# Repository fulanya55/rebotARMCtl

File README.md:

# rebotARMCtl

机械臂采集部署平台与 STM32 同步控制器，面向 reBot Arm B601-RS 与 Star Arm 102。

> **当前状态：软件、固件和 PCB 设计已完成，但都还没有接触过真实硬件。** 固件只在 PC 上的仿真器里运行过，STM32 镜像只完成了编译和结构检查，电路板还没有打样。第一次接机械臂前，请按 [docs/bringup.md](docs/bringup.md) 一步步做。

## 没有硬件时先跑起来

需要 [uv](https://docs.astral.sh/uv/) 和 Node.js。

```bash
uv sync
cd apps/lab/frontend && npm ci && npm run build && cd ../../..
uv run rac up --sim
```

打开 <http://127.0.0.1:8000/controller>。`--sim` 用的是真实的固件核心加一个机械臂仿真器，协议和总线时序都按真实设备走。接上控制器后，把 `--sim` 去掉即可。

## 能做什么

| 需求 | 功能 | 位置 |
| --- | --- | --- |
| 1.1 设备连接 | 控制器发现和重连、端口型号识别、机械臂绑定、相机预览和保存绑定 | 控制台「设备」页 |
| 1.2 关节校准 | 按序列号保存的校准版本，零位、方向、行程范围和夹爪标定，单关节验证 | 「校准」页 |
| 1.3 主从同步 | **在 STM32 上本地闭环**，PC 的卡顿不影响跟随；PC 断开 500 ms 后全部机械臂进入保持 | `firmware/core` |
| 1.4 可视化示教 | URDF 三维视图、关节滑块和拖动、末端拖动（PC 上解 IK）、示教点、RS 拖动示教 | 「示教」页 |
| 1.5 模型部署 | LeRobot 和 StarVLA 后端，模型放在独立进程里 | `packages/rac-policy` |
| 1.6 人工干预 | 接管和交还，过期令牌和旧代次的指令一律被拒绝 | 「模型」页 |
| 1.7 真机回放 | 从任意时间点回放，先缓慢靠近起点 | 「回放」页 |
| 1.8 统一运行控制 | 所有页面共用的状态条，停止和急停始终可用 | `RunBar` |
| 2.1–2.5 数据 | LeRobot Dataset v3 录制、原始时间线、标注、导入导出合并、浏览 | `packages/rac-data` |
| 3.1–3.3 控制器 | 2 路 CAN、2 路 UART、1 路 USB，带版本的 RAC-Link 协议，Python SDK | `firmware/`、`packages/rac-link` |

基础配置是 2 台 reBot RS 从臂加 2 台 Star 主臂。原有 MakerMods Lab 的页面和流程也保留了。`controller` 类型的机器人可以在 Lab 里遥操作和录制；回放和模型部署请用控制台页面，Lab 会直接提示，因为它的缓入逻辑按角度计算，不适用于这里以弧度工作的机械臂。

## 目录

```
apps/lab/             MakerMods Lab（已内嵌）加控制器页面和路由
packages/rac-link/    协议、传输层、Python SDK
packages/rac-service/ Controller Service，USB 的唯一持有者
packages/rac-kinematics/  URDF、正逆运动学、轨迹
packages/rac-camera/  相机进程和共享内存
packages/rac-data/    录制、LeRobot 数据集、标注
packages/rac-policy/  模型进程
packages/rac-lerobot/ LeRobot 的 Robot 和 Teleoperator 代理
firmware/core/        可移植的固件核心
firmware/port/        stm32g4（真机）和 sil（仿真）
hardware/sync-controller/  硬件选型、KiCad 工程、制造文件
tools/                协议生成、固件构建
```

设计说明见 [docs/architecture.md](docs/architecture.md)，协议见 [docs/protocol.md](docs/protocol.md)，硬件见 [hardware/sync-controller/README.md](hardware/sync-controller/README.md)。

## 常用命令

```bash
uv run pytest tests                              # 全部集成测试
uv run python tools/build_firmware.py test       # 固件核心的行为测试
uv run python tools/build_firmware.py stm32      # 交叉编译（先运行 tools/fetch_firmware_deps.py）
uv run python tools/gen_protocol.py              # 改协议后重新生成 C 和 Python
uv run python hardware/sync-controller/gen/make_all.py  # 重新生成并检查整块板子
PYTHONUTF8=1 uv run python tests/e2e/run_web_e2e.py --out <目录>  # 浏览器走查（先启动平台）
```

交叉编译用的是 `ziglang`，由 uv 管理，不需要另装 ARM 工具链。硬件部分需要 KiCad 10，路径不同时设置 `KICAD_CLI` 和 `KICAD_PYTHON`。

Lab 自带的测试要在 `apps/lab` 目录下运行，并设置 `PYTHONUTF8=1`。Windows 上有 72 个测试失败，引入控制器之前就是这 72 个，主要和路径、进程管理的平台差异有关。

## 许可

本仓库只用于个人学习，**请保持私有**：里面有几项上游没有授予再分发权利的文件。复用了哪些项目、公开前要清掉什么，都写在 [docs/LICENSE_AUDIT.md](docs/LICENSE_AUDIT.md)。代码暂定 Apache-2.0，`assets/robots/rebot_b601_rs` 沿用其 CERN-OHL-W-2.0，内嵌的 Lab 保留其上游许可。

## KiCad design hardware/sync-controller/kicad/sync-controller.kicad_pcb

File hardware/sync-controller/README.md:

# 同步控制器硬件

STM32G474 主控，2 路隔离 CAN、2 路隔离舵机 UART、USB-C、急停回路和继电器输出。116 × 90 mm，4 层板。

**这块板子还没有打样，也没有上电。** 下面的检查都是设计规则层面的，不能代替实物验证。

## 文件

| 路径 | 内容 |
| --- | --- |
| `docs/selection.md` | 选型依据，每项都写了来源 |
| `docs/bom.csv` | 物料清单。LCSC 编号留空表示还没确认，下单前要逐项核对 |
| `docs/schematic.pdf`、`docs/board_top.png` | 原理图和渲染图 |
| `gen/design.py` | **唯一的设计数据**，原理图和 PCB 都从这里生成 |
| `kicad/` | 生成的 KiCad 工程，可以直接用 KiCad 打开 |
| `fab/` | Gerber、钻孔和贴片坐标 |

## 重新生成

```bash
uv run python hardware/sync-controller/gen/make_all.py
```

顺序是原理图 → BOM → ERC → 网表比对 → 布局布线 → DRC 和原理图一致性 → 隔离带测量 → 制造文件，任何一步失败就停。布线要几分钟，`--skip-route` 可以保留现有布局。

修改设计请改 `gen/design.py` 或 `gen/gen_pcb.py`。直接在 KiCad 里改的内容，下次生成时会被覆盖；如果决定以后手工维护 PCB，就不要再运行布线这一步。

## 关键设计

- **每路接口独立隔离。** CAN 用 ISO1044BD，UART 用 ADuM1201BRZ，电源用 B0509S-1WR3 加 HT7550-1 稳压。没有用 5 V 输入 5 V 输出的模块，因为它轻载时电压可能超过 ISO1044 VCC2 的 5.5 V 上限。
- **控制板不从机械臂取电。** Star 的 3 针舵机座中间的电源针没有连接。隔离侧由板上的 DC/DC 供电。
- **急停是硬件回路。** 常闭急停触点和继电器线圈串联，按下后不经过任何软件就会释放。MCU 复位时栅极的下拉同样会让继电器释放。两路检测信号让固件也能知道发生了什么。
- **继电器只给信号用。** G5V-2 不能切断 48 V 电机电流，请用它去控制外部的接触器或驱动器使能。

## 布线

这块板子的布线由 `gen/gen_pcb.py` 里自己写的栅格 A* 布线器完成，带拆线重布和隔离域约束。它能保证 DRC 通过，但不会像有经验的工程师那样考虑回流路径、串扰和散热。**打样前请人工审一遍版图**，重点看 USB 差分对、CAN 差分对、DC/DC 周围和跨隔离带的区域。

## 打样前还要确认

- BOM 里 LCSC 编号为空的物料，以及所有封装和实物的对应关系
- Star 线束的针脚顺序和逻辑电平（目前来自公开资料，未用实物验证）
- 隔离带 1.00 mm 是**功能隔离**，不是安全隔离，不能当作安规爬电距离
- 嘉立创等厂家的 4 层板叠层和阻抗参数。USB 差分对没有做阻抗计算
- 板上没有放光学定位点（fiducial）。要贴片的话，确认厂家能接受或自行添加
- 急停端子不接急停按钮时，板子会一直处于急停状态，继电器不吸合。这是故意的，接线方法见 `docs/bringup.md` 第 2 步

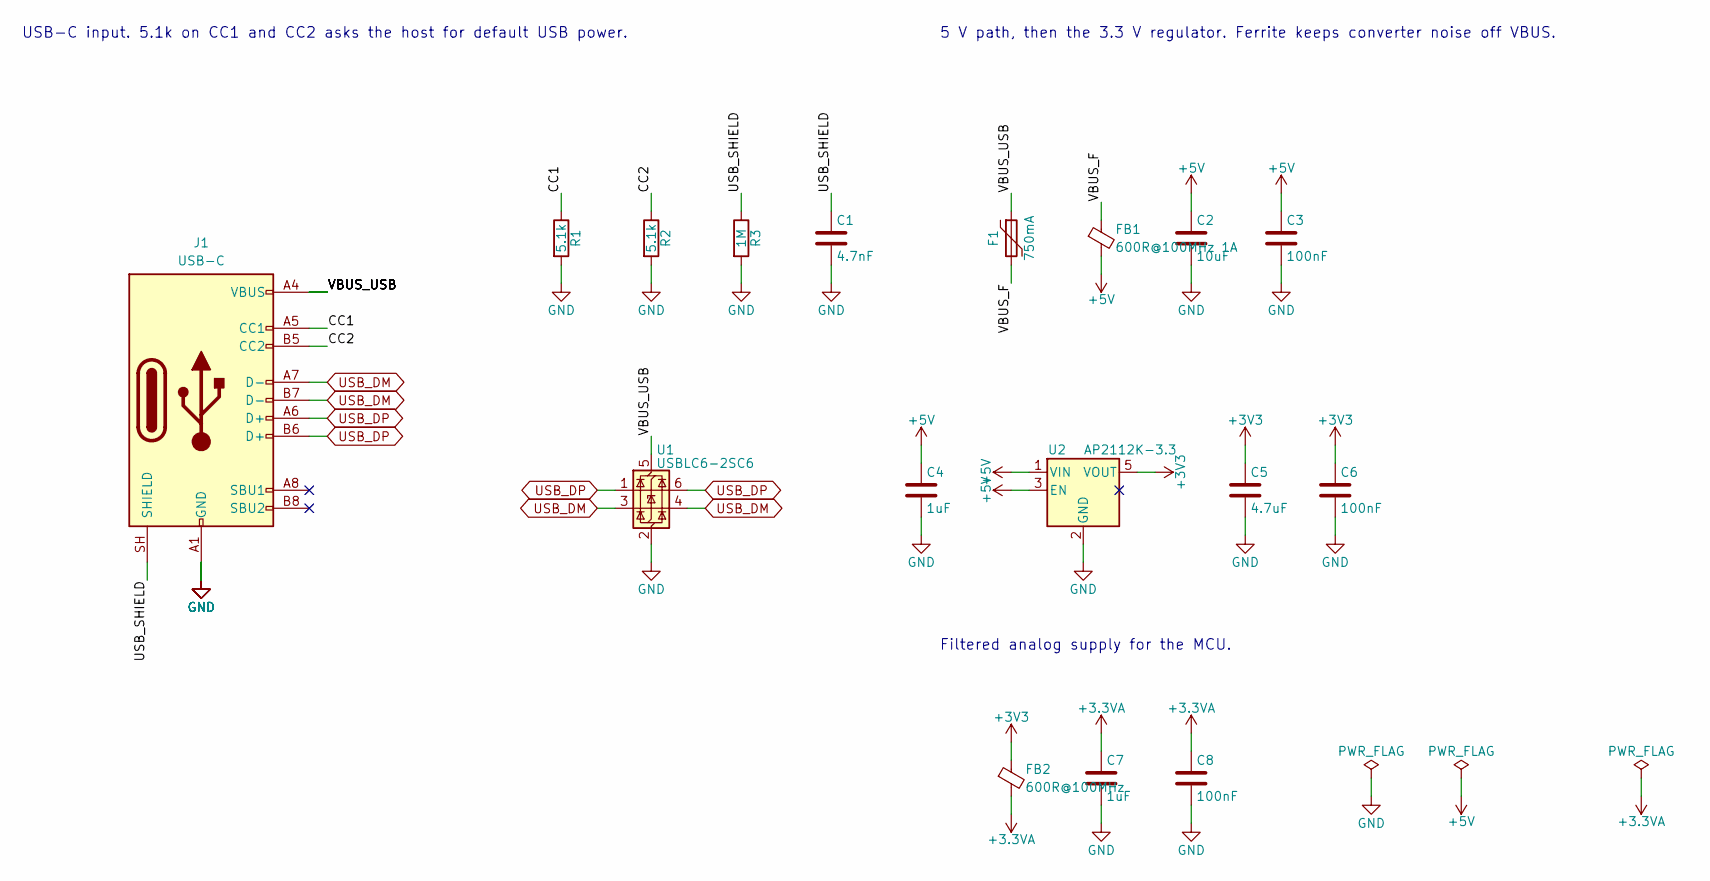
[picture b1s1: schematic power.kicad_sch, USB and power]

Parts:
C1: 4.7nF; C_0603_1608Metric
C2: 10uF; C_0805_2012Metric
C3, C6, C8: 100nF; C_0603_1608Metric
C4, C7: 1uF; C_0603_1608Metric
C5: 4.7uF; C_0805_2012Metric
F1: 750mA; Fuse_1206_3216Metric; MPN SMD1206 750mA hold
FB1: 600R@100MHz 1A; L_0805_2012Metric
FB2: 600R@100MHz; L_0603_1608Metric
J1: USB-C; USB_C_Receptacle_HRO_TYPE-C-31-M-12; MPN HRO TYPE-C-31-M-12; LCSC C165948
R1, R2: 5.1k; R_0603_1608Metric
R3: 1M; R_0603_1608Metric
U1: USBLC6-2SC6; SOT-23-6; MPN USBLC6-2SC6
U2: AP2112K-3.3; SOT-23-5; MPN AP2112K-3.3TRG1

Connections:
+3.3VA: C7.1, C8.1, FB2.2; also elsewhere on the board
+3V3: C5.1, C6.1, FB2.1, U2.5 (VOUT); also elsewhere on the board
+5V: C2.1, C3.1, C4.1, FB1.2, U2.1 (VIN), U2.3 (EN); also elsewhere on the board
/USB and power/CC1: J1.A5 (CC1), R1.1
/USB and power/CC2: J1.B5 (CC2), R2.1
/USB and power/USB_SHIELD: C1.1, J1.SH (SHIELD), R3.1
/USB and power/VBUS_F: F1.2, FB1.1
/USB and power/VBUS_USB: F1.1, J1.A4 (VBUS), J1.A9 (VBUS), J1.B4 (VBUS), J1.B9 (VBUS), U1.5 (VBUS)
GND: C1.2, C2.2, C3.2, C4.2, C5.2, C6.2, C7.2, C8.2, J1.A1 (GND), J1.A12 (GND), J1.B1 (GND), J1.B12 (GND), R1.2, R2.2, R3.2, U1.2 (GND), U2.2 (GND); also elsewhere on the board
USB_DM: J1.A7 (D-), J1.B7 (D-), U1.3 (I/O2), U1.4 (I/O2); also elsewhere on the board
USB_DP: J1.A6 (D+), J1.B6 (D+), U1.1 (I/O1), U1.6 (I/O1); also elsewhere on the board

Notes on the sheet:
USB-C input. 5.1k on CC1 and CC2 asks the host for default USB power.
5 V path, then the 3.3 V regulator. Ferrite keeps converter noise off VBUS.
Filtered analog supply for the MCU.

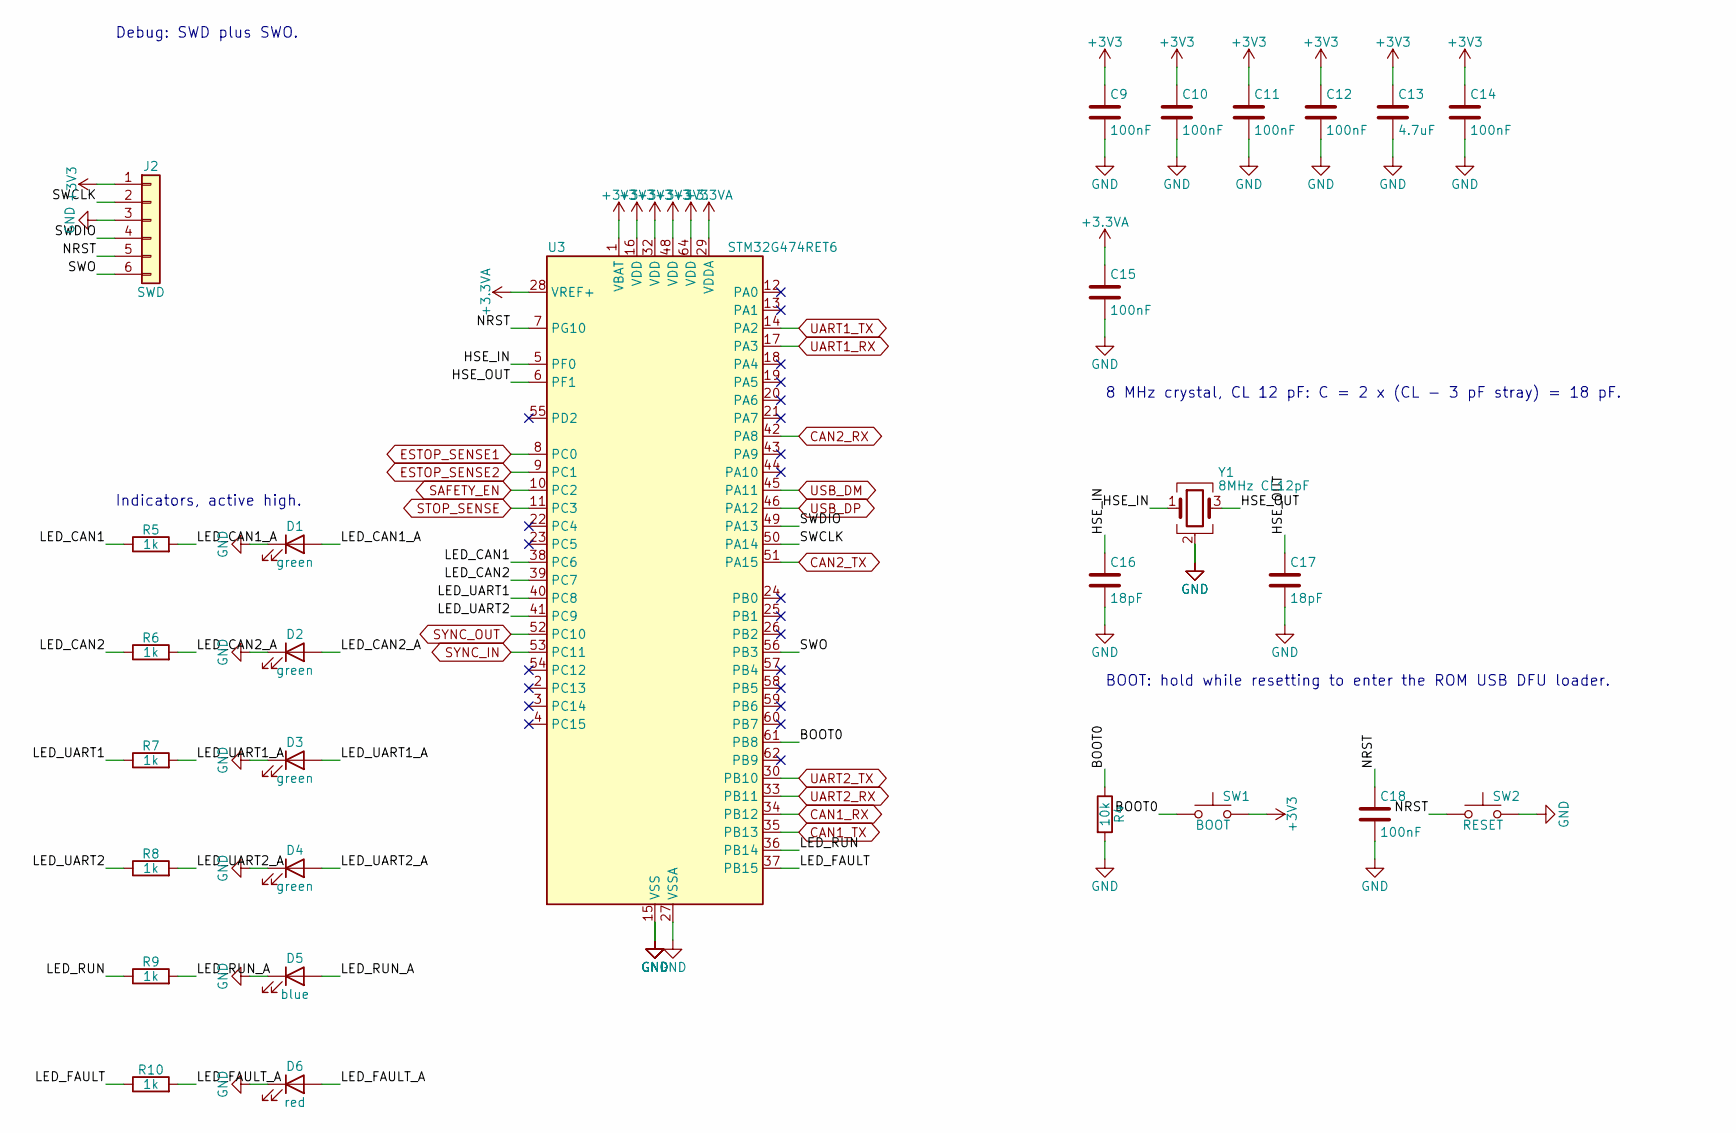
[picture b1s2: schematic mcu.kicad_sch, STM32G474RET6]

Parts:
C9, C10, C11, C12, C14, C15, C18: 100nF; C_0603_1608Metric
C13: 4.7uF; C_0805_2012Metric
C16, C17: 18pF; C_0603_1608Metric
D1, D2, D3, D4: green; LED_0603_1608Metric
D5: blue; LED_0603_1608Metric
D6: red; LED_0603_1608Metric
J2: SWD; PinHeader_1x06_P2.54mm_Vertical
R4: 10k; R_0603_1608Metric
R5, R6, R7, R8, R9, R10: 1k; R_0603_1608Metric
SW1: BOOT; SW_PUSH_6mm
SW2: RESET; SW_PUSH_6mm
U3: STM32G474RET6; LQFP-64_10x10mm_P0.5mm; MPN STM32G474RET6
Y1: 8MHz CL12pF; Crystal_SMD_3225-4Pin_3.2x2.5mm; MPN 8 MHz 3225 12 pF

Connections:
+3.3VA: C15.1, U3.28 (VREF+), U3.29 (VDDA); also elsewhere on the board
+3V3: C9.1, C10.1, C11.1, C12.1, C13.1, C14.1, J2.1, SW1.2, U3.1 (VBAT), U3.16 (VDD), U3.32 (VDD), U3.48 (VDD), U3.64 (VDD); also elsewhere on the board
/STM32G474RET6/BOOT0: R4.1, SW1.1, U3.61 (PB8)
/STM32G474RET6/HSE_IN: C16.1, U3.5 (PF0), Y1.1
/STM32G474RET6/HSE_OUT: C17.1, U3.6 (PF1), Y1.3
/STM32G474RET6/LED_CAN1: R5.1, U3.38 (PC6)
/STM32G474RET6/LED_CAN1_A: D1.2 (A), R5.2
/STM32G474RET6/LED_CAN2: R6.1, U3.39 (PC7)
/STM32G474RET6/LED_CAN2_A: D2.2 (A), R6.2
/STM32G474RET6/LED_FAULT: R10.1, U3.37 (PB15)
/STM32G474RET6/LED_FAULT_A: D6.2 (A), R10.2
/STM32G474RET6/LED_RUN: R9.1, U3.36 (PB14)
/STM32G474RET6/LED_RUN_A: D5.2 (A), R9.2
/STM32G474RET6/LED_UART1: R7.1, U3.40 (PC8)
/STM32G474RET6/LED_UART1_A: D3.2 (A), R7.2
/STM32G474RET6/LED_UART2: R8.1, U3.41 (PC9)
/STM32G474RET6/LED_UART2_A: D4.2 (A), R8.2
/STM32G474RET6/NRST: C18.1, J2.5, SW2.1, U3.7 (PG10)
/STM32G474RET6/SWCLK: J2.2, U3.50 (PA14)
/STM32G474RET6/SWDIO: J2.4, U3.49 (PA13)
/STM32G474RET6/SWO: J2.6, U3.56 (PB3)
CAN1_RX: U3.34 (PB12); also elsewhere on the board
CAN1_TX: U3.35 (PB13); also elsewhere on the board
CAN2_RX: U3.42 (PA8); also elsewhere on the board
CAN2_TX: U3.51 (PA15); also elsewhere on the board
ESTOP_SENSE1: U3.8 (PC0); also elsewhere on the board
ESTOP_SENSE2: U3.9 (PC1); also elsewhere on the board
GND: C9.2, C10.2, C11.2, C12.2, C13.2, C14.2, C15.2, C16.2, C17.2, C18.2, D1.1 (K), D2.1 (K), D3.1 (K), D4.1 (K), D5.1 (K), D6.1 (K), J2.3, R4.2, SW2.2, U3.15 (VSS), U3.27 (VSSA), U3.31 (VSS), U3.47 (VSS), U3.63 (VSS), Y1.2 (G), Y1.4 (G); also elsewhere on the board
SAFETY_EN: U3.10 (PC2); also elsewhere on the board
STOP_SENSE: U3.11 (PC3); also elsewhere on the board
SYNC_IN: U3.53 (PC11); also elsewhere on the board
SYNC_OUT: U3.52 (PC10); also elsewhere on the board
UART1_RX: U3.17 (PA3); also elsewhere on the board
UART1_TX: U3.14 (PA2); also elsewhere on the board
UART2_RX: U3.33 (PB11); also elsewhere on the board
UART2_TX: U3.30 (PB10); also elsewhere on the board
USB_DM: U3.45 (PA11); also elsewhere on the board
USB_DP: U3.46 (PA12); also elsewhere on the board

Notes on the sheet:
8 MHz crystal, CL 12 pF: C = 2 x (CL - 3 pF stray) = 18 pF.
BOOT: hold while resetting to enter the ROM USB DFU loader.
Debug: SWD plus SWO.
Indicators, active high.

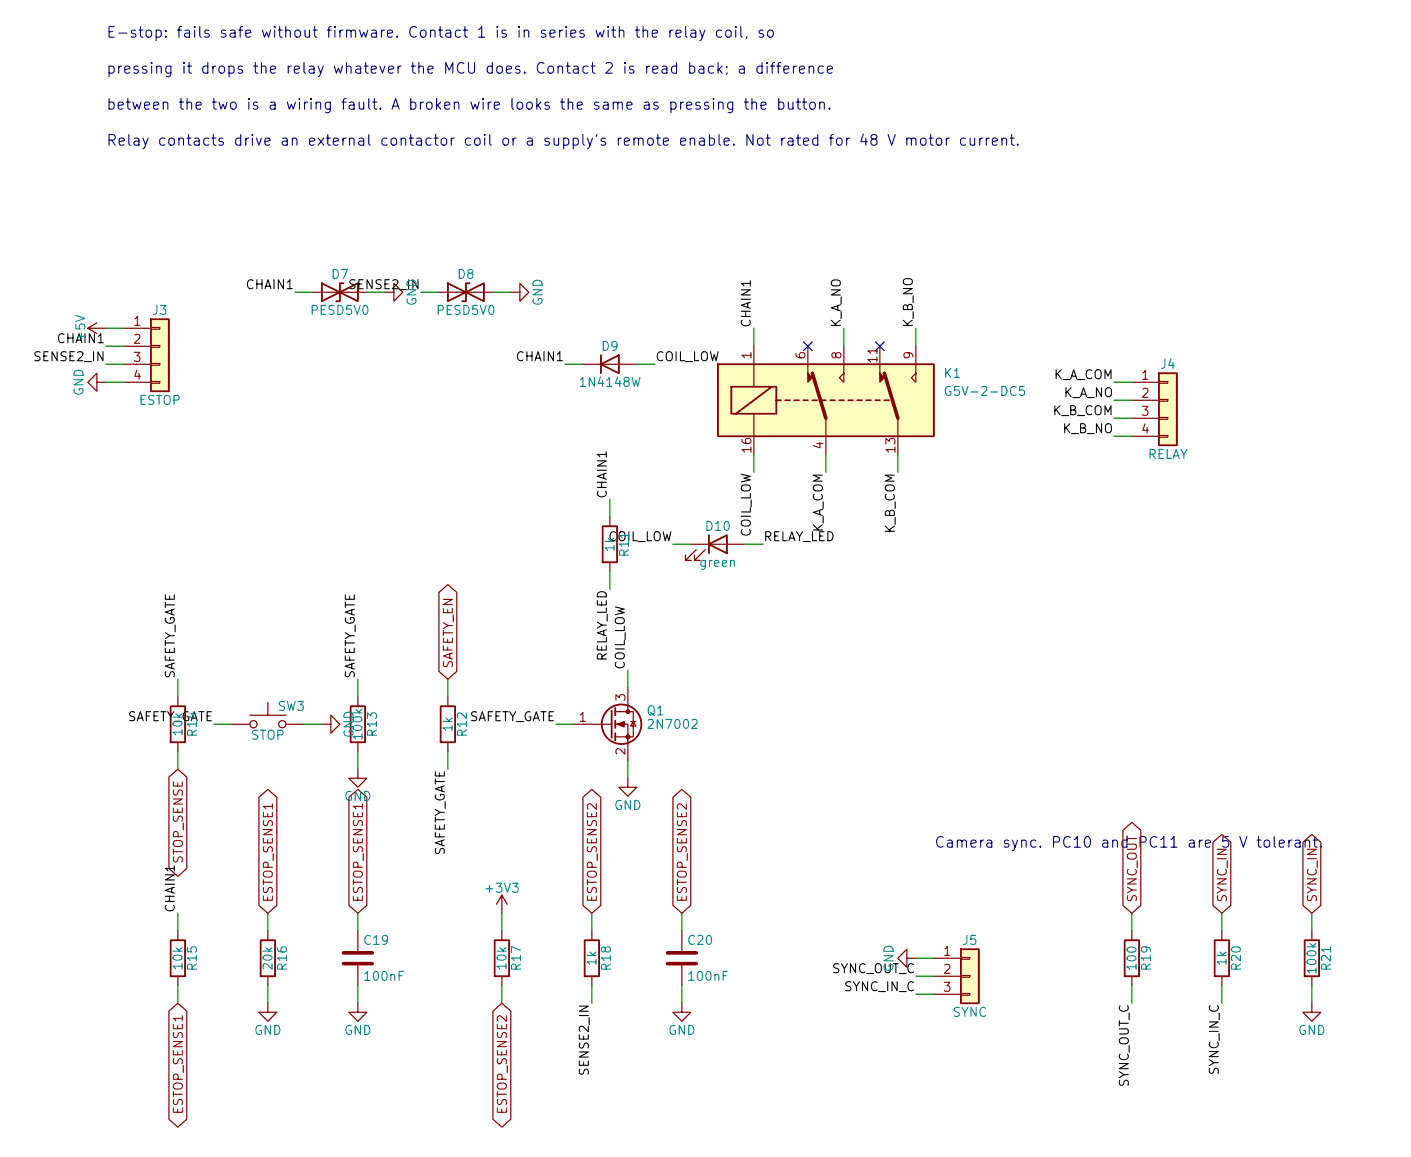
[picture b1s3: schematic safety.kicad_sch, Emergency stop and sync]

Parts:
C19, C20: 100nF; C_0603_1608Metric
D7, D8: PESD5V0; D_SOD-323
D9: 1N4148W; D_SOD-323
D10: green; LED_0603_1608Metric
J3: ESTOP; PhoenixContact_MC_1,5_4-G-3.5_1x04_P3.50mm_Horizontal
J4: RELAY; PhoenixContact_MC_1,5_4-G-3.5_1x04_P3.50mm_Horizontal
J5: SYNC; PinHeader_1x03_P2.54mm_Vertical
K1: G5V-2-DC5; Relay_DPDT_Omron_G5V-2; MPN Omron G5V-2 DC5
Q1: 2N7002; SOT-23; MPN 2N7002
R11, R12, R18, R20: 1k; R_0603_1608Metric
R13, R21: 100k; R_0603_1608Metric
R14, R15, R17: 10k; R_0603_1608Metric
R16: 20k; R_0603_1608Metric
R19: 100; R_0603_1608Metric
SW3: STOP; SW_PUSH_6mm

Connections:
+3V3: R17.1; also elsewhere on the board
+5V: J3.1; also elsewhere on the board
/Emergency stop and sync/CHAIN1: D7.1 (A1), D9.1 (K), J3.2, K1.1, R11.1, R15.1
/Emergency stop and sync/COIL_LOW: D9.2 (A), D10.1 (K), K1.16, Q1.3 (D)
/Emergency stop and sync/K_A_COM: J4.1, K1.4
/Emergency stop and sync/K_A_NO: J4.2, K1.8
/Emergency stop and sync/K_B_COM: J4.3, K1.13
/Emergency stop and sync/K_B_NO: J4.4, K1.9
/Emergency stop and sync/RELAY_LED: D10.2 (A), R11.2
/Emergency stop and sync/SAFETY_GATE: Q1.1 (G), R12.2, R13.1, R14.1, SW3.1
/Emergency stop and sync/SENSE2_IN: D8.1 (A1), J3.3, R18.2
/Emergency stop and sync/SYNC_IN_C: J5.3, R20.2
/Emergency stop and sync/SYNC_OUT_C: J5.2, R19.2
ESTOP_SENSE1: C19.1, R15.2, R16.1; also elsewhere on the board
ESTOP_SENSE2: C20.1, R17.2, R18.1; also elsewhere on the board
GND: C19.2, C20.2, D7.2 (A2), D8.2 (A2), J3.4, J5.1, Q1.2 (S), R13.2, R16.2, R21.2, SW3.2; also elsewhere on the board
SAFETY_EN: R12.1; also elsewhere on the board
STOP_SENSE: R14.2; also elsewhere on the board
SYNC_IN: R20.1, R21.1; also elsewhere on the board
SYNC_OUT: R19.1; also elsewhere on the board

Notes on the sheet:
E-stop: fails safe without firmware. Contact 1 is in series with the relay coil, so
pressing it drops the relay whatever the MCU does. Contact 2 is read back; a difference
between the two is a wiring fault. A broken wire looks the same as pressing the button.
Relay contacts drive an external contactor coil or a supply's remote enable. Not rated for 48 V motor current.
Camera sync. PC10 and PC11 are 5 V tolerant.

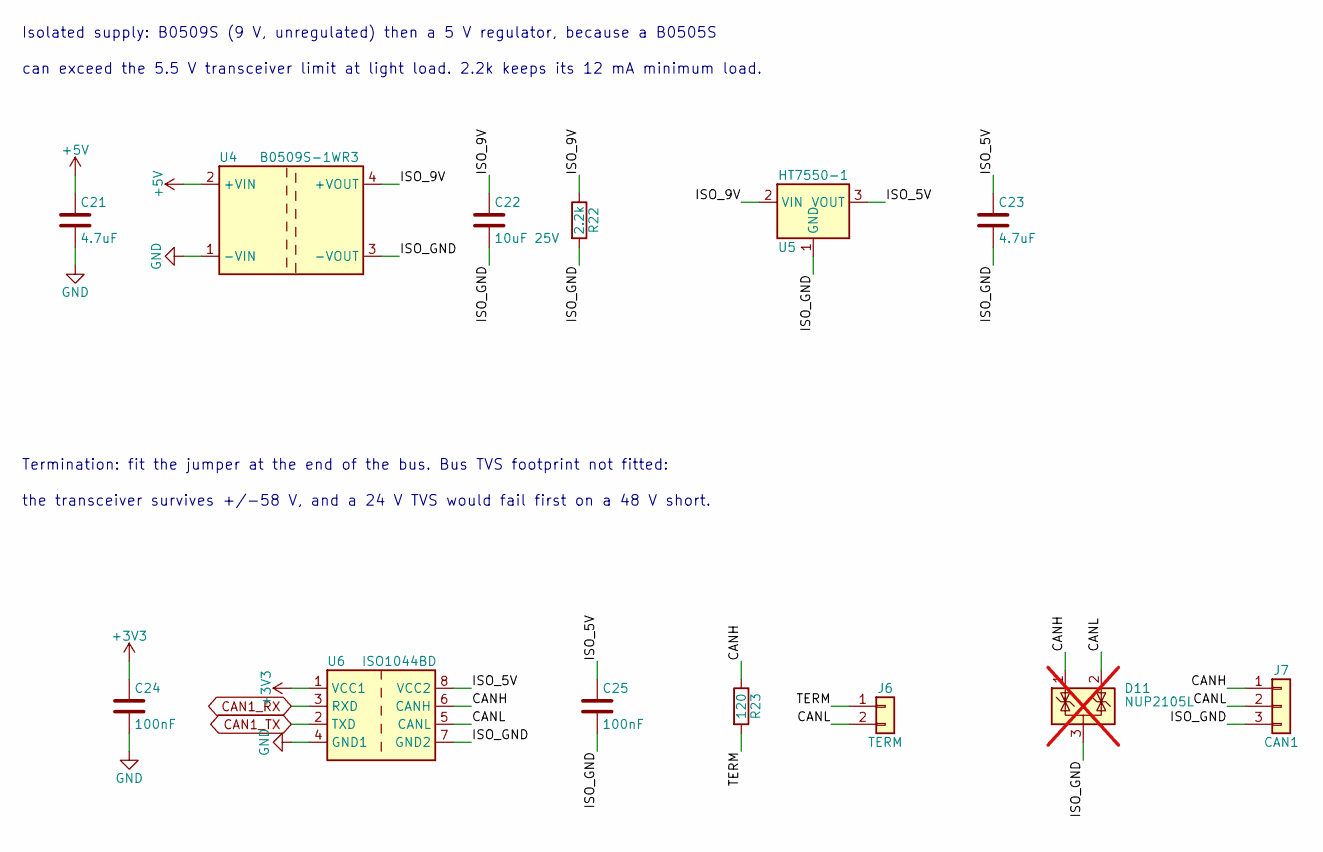
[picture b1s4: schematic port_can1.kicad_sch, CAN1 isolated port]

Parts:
C21, C23: 4.7uF; C_0805_2012Metric
C22: 10uF 25V; C_0805_2012Metric
C24, C25: 100nF; C_0603_1608Metric
D11: NUP2105L; SOT-23; not fitted
J6: TERM; PinHeader_1x02_P2.54mm_Vertical
J7: CAN1; PhoenixContact_MC_1,5_3-G-3.5_1x03_P3.50mm_Horizontal
R22: 2.2k; R_0603_1608Metric
R23: 120; R_0603_1608Metric
U4: B0509S-1WR3; Converter_DCDC_Murata_CRE1xxxxxxSC_THT; MPN Mornsun B0509S-1WR3
U5: HT7550-1; SOT-89-3; MPN HT7550-1
U6: ISO1044BD; SOIC-8_3.9x4.9mm_P1.27mm; MPN ISO1044BD; LCSC C2878198

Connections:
+3V3: C24.1, U6.1 (VCC1); also elsewhere on the board
+5V: C21.1, U4.2 (+VIN); also elsewhere on the board
/CAN1 isolated port/CANH: D11.1 (K), J7.1, R23.1, U6.6 (CANH)
/CAN1 isolated port/CANL: D11.2 (K), J6.2, J7.2, U6.5 (CANL)
/CAN1 isolated port/ISO_5V: C23.1, C25.1, U5.3 (VOUT), U6.8 (VCC2)
/CAN1 isolated port/ISO_9V: C22.1, R22.1, U4.4 (+VOUT), U5.2 (VIN)
/CAN1 isolated port/ISO_GND: C22.2, C23.2, C25.2, D11.3 (A), J7.3, R22.2, U4.3 (-VOUT), U5.1 (GND), U6.7 (GND2)
/CAN1 isolated port/TERM: J6.1, R23.2
CAN1_RX: U6.3 (RXD); also elsewhere on the board
CAN1_TX: U6.2 (TXD); also elsewhere on the board
GND: C21.2, C24.2, U4.1 (-VIN), U6.4 (GND1); also elsewhere on the board

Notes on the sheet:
Isolated supply: B0509S (9 V, unregulated) then a 5 V regulator, because a B0505S
can exceed the 5.5 V transceiver limit at light load. 2.2k keeps its 12 mA minimum load.
Termination: fit the jumper at the end of the bus. Bus TVS footprint not fitted:
the transceiver survives +/-58 V, and a 24 V TVS would fail first on a 48 V short.

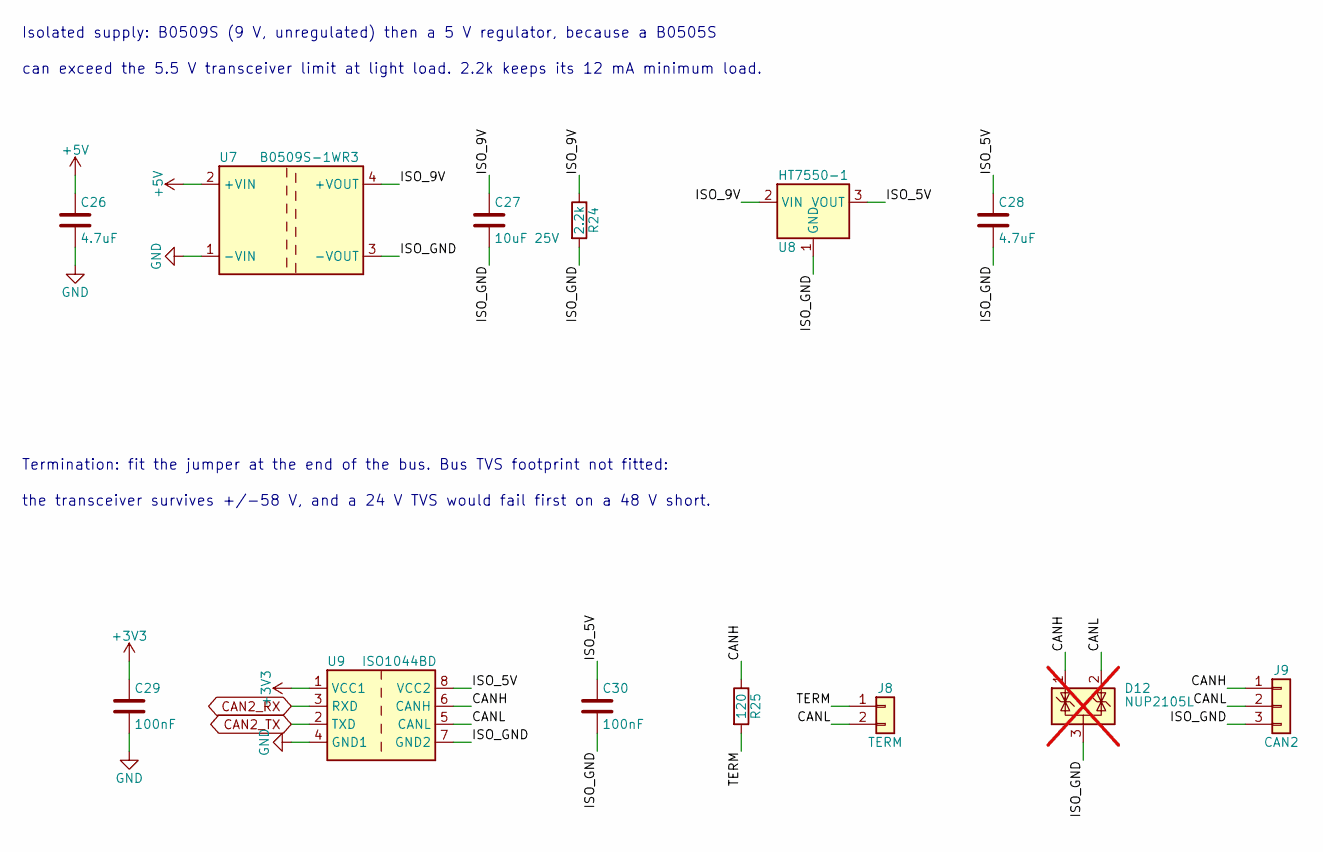
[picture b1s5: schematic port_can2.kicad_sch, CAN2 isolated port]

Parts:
C26, C28: 4.7uF; C_0805_2012Metric
C27: 10uF 25V; C_0805_2012Metric
C29, C30: 100nF; C_0603_1608Metric
D12: NUP2105L; SOT-23; not fitted
J8: TERM; PinHeader_1x02_P2.54mm_Vertical
J9: CAN2; PhoenixContact_MC_1,5_3-G-3.5_1x03_P3.50mm_Horizontal
R24: 2.2k; R_0603_1608Metric
R25: 120; R_0603_1608Metric
U7: B0509S-1WR3; Converter_DCDC_Murata_CRE1xxxxxxSC_THT; MPN Mornsun B0509S-1WR3
U8: HT7550-1; SOT-89-3; MPN HT7550-1
U9: ISO1044BD; SOIC-8_3.9x4.9mm_P1.27mm; MPN ISO1044BD; LCSC C2878198

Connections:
+3V3: C29.1, U9.1 (VCC1); also elsewhere on the board
+5V: C26.1, U7.2 (+VIN); also elsewhere on the board
/CAN2 isolated port/CANH: D12.1 (K), J9.1, R25.1, U9.6 (CANH)
/CAN2 isolated port/CANL: D12.2 (K), J8.2, J9.2, U9.5 (CANL)
/CAN2 isolated port/ISO_5V: C28.1, C30.1, U8.3 (VOUT), U9.8 (VCC2)
/CAN2 isolated port/ISO_9V: C27.1, R24.1, U7.4 (+VOUT), U8.2 (VIN)
/CAN2 isolated port/ISO_GND: C27.2, C28.2, C30.2, D12.3 (A), J9.3, R24.2, U7.3 (-VOUT), U8.1 (GND), U9.7 (GND2)
/CAN2 isolated port/TERM: J8.1, R25.2
CAN2_RX: U9.3 (RXD); also elsewhere on the board
CAN2_TX: U9.2 (TXD); also elsewhere on the board
GND: C26.2, C29.2, U7.1 (-VIN), U9.4 (GND1); also elsewhere on the board

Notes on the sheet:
Isolated supply: B0509S (9 V, unregulated) then a 5 V regulator, because a B0505S
can exceed the 5.5 V transceiver limit at light load. 2.2k keeps its 12 mA minimum load.
Termination: fit the jumper at the end of the bus. Bus TVS footprint not fitted:
the transceiver survives +/-58 V, and a 24 V TVS would fail first on a 48 V short.

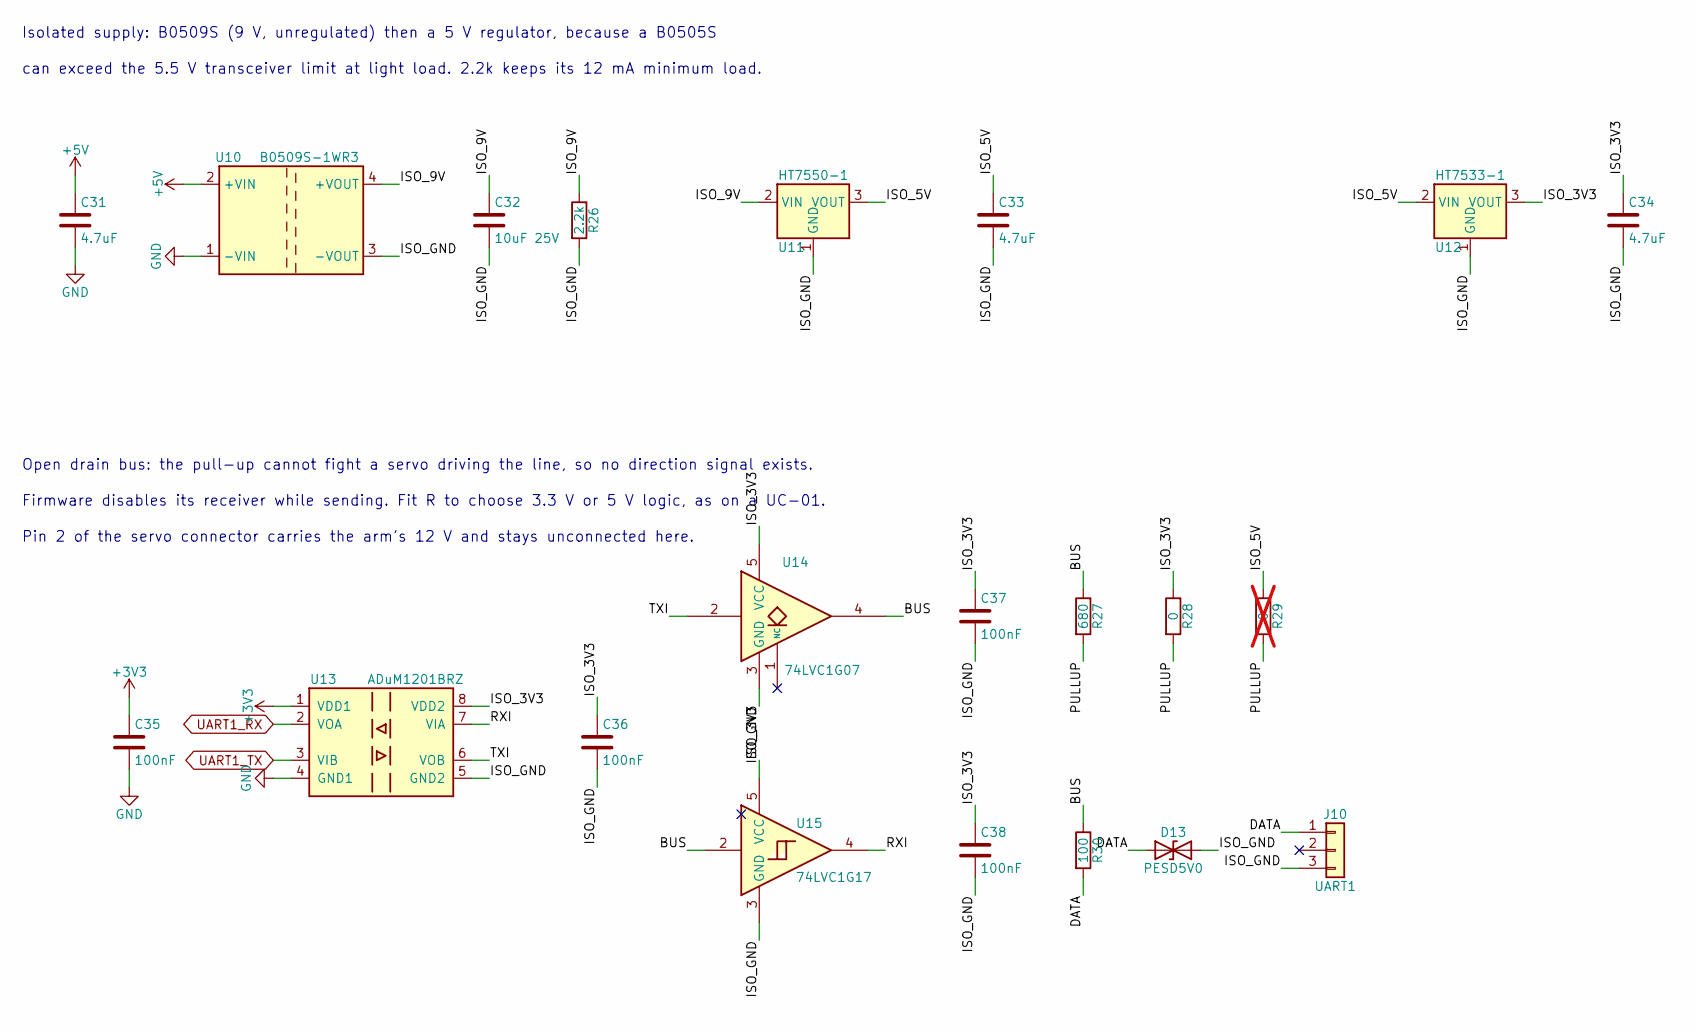
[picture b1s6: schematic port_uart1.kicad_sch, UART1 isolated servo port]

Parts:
C31, C33, C34: 4.7uF; C_0805_2012Metric
C32: 10uF 25V; C_0805_2012Metric
C35, C36, C37, C38: 100nF; C_0603_1608Metric
D13: PESD5V0; D_SOD-323
J10: UART1; JST_PH_B3B-PH-K_1x03_P2.00mm_Vertical
R26: 2.2k; R_0603_1608Metric
R27: 680; R_0603_1608Metric
R28: 0; R_0603_1608Metric
R29: 0; R_0603_1608Metric; not fitted
R30: 100; R_0603_1608Metric
U10: B0509S-1WR3; Converter_DCDC_Murata_CRE1xxxxxxSC_THT; MPN Mornsun B0509S-1WR3
U11: HT7550-1; SOT-89-3; MPN HT7550-1
U12: HT7533-1; SOT-89-3; MPN HT7533-1
U13: ADuM1201BRZ; SOIC-8_3.9x4.9mm_P1.27mm; MPN ADuM1201BRZ
U14: 74LVC1G07; SOT-23-5; MPN SN74LVC1G07DBVR
U15: 74LVC1G17; SOT-23-5; MPN SN74LVC1G17DBVR

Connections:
+3V3: C35.1, U13.1 (VDD1); also elsewhere on the board
+5V: C31.1, U10.2 (+VIN); also elsewhere on the board
/UART1 isolated servo port/BUS: R27.1, R30.1, U14.4, U15.2
/UART1 isolated servo port/DATA: D13.1 (A1), J10.1, R30.2
/UART1 isolated servo port/ISO_3V3: C34.1, C36.1, C37.1, C38.1, R28.1, U12.3 (VOUT), U13.8 (VDD2), U14.5 (VCC), U15.5 (VCC)
/UART1 isolated servo port/ISO_5V: C33.1, R29.1, U11.3 (VOUT), U12.2 (VIN)
/UART1 isolated servo port/ISO_9V: C32.1, R26.1, U10.4 (+VOUT), U11.2 (VIN)
/UART1 isolated servo port/ISO_GND: C32.2, C33.2, C34.2, C36.2, C37.2, C38.2, D13.2 (A2), J10.3, R26.2, U10.3 (-VOUT), U11.1 (GND), U12.1 (GND), U13.5 (GND2), U14.3 (GND), U15.3 (GND)
/UART1 isolated servo port/PULLUP: R27.2, R28.2, R29.2
/UART1 isolated servo port/RXI: U13.7 (VIA), U15.4
/UART1 isolated servo port/TXI: U13.6 (VOB), U14.2
GND: C31.2, C35.2, U10.1 (-VIN), U13.4 (GND1); also elsewhere on the board
UART1_RX: U13.2 (VOA); also elsewhere on the board
UART1_TX: U13.3 (VIB); also elsewhere on the board

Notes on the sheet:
Isolated supply: B0509S (9 V, unregulated) then a 5 V regulator, because a B0505S
can exceed the 5.5 V transceiver limit at light load. 2.2k keeps its 12 mA minimum load.
Open drain bus: the pull-up cannot fight a servo driving the line, so no direction signal exists.
Firmware disables its receiver while sending. Fit R to choose 3.3 V or 5 V logic, as on a UC-01.
Pin 2 of the servo connector carries the arm's 12 V and stays unconnected here.

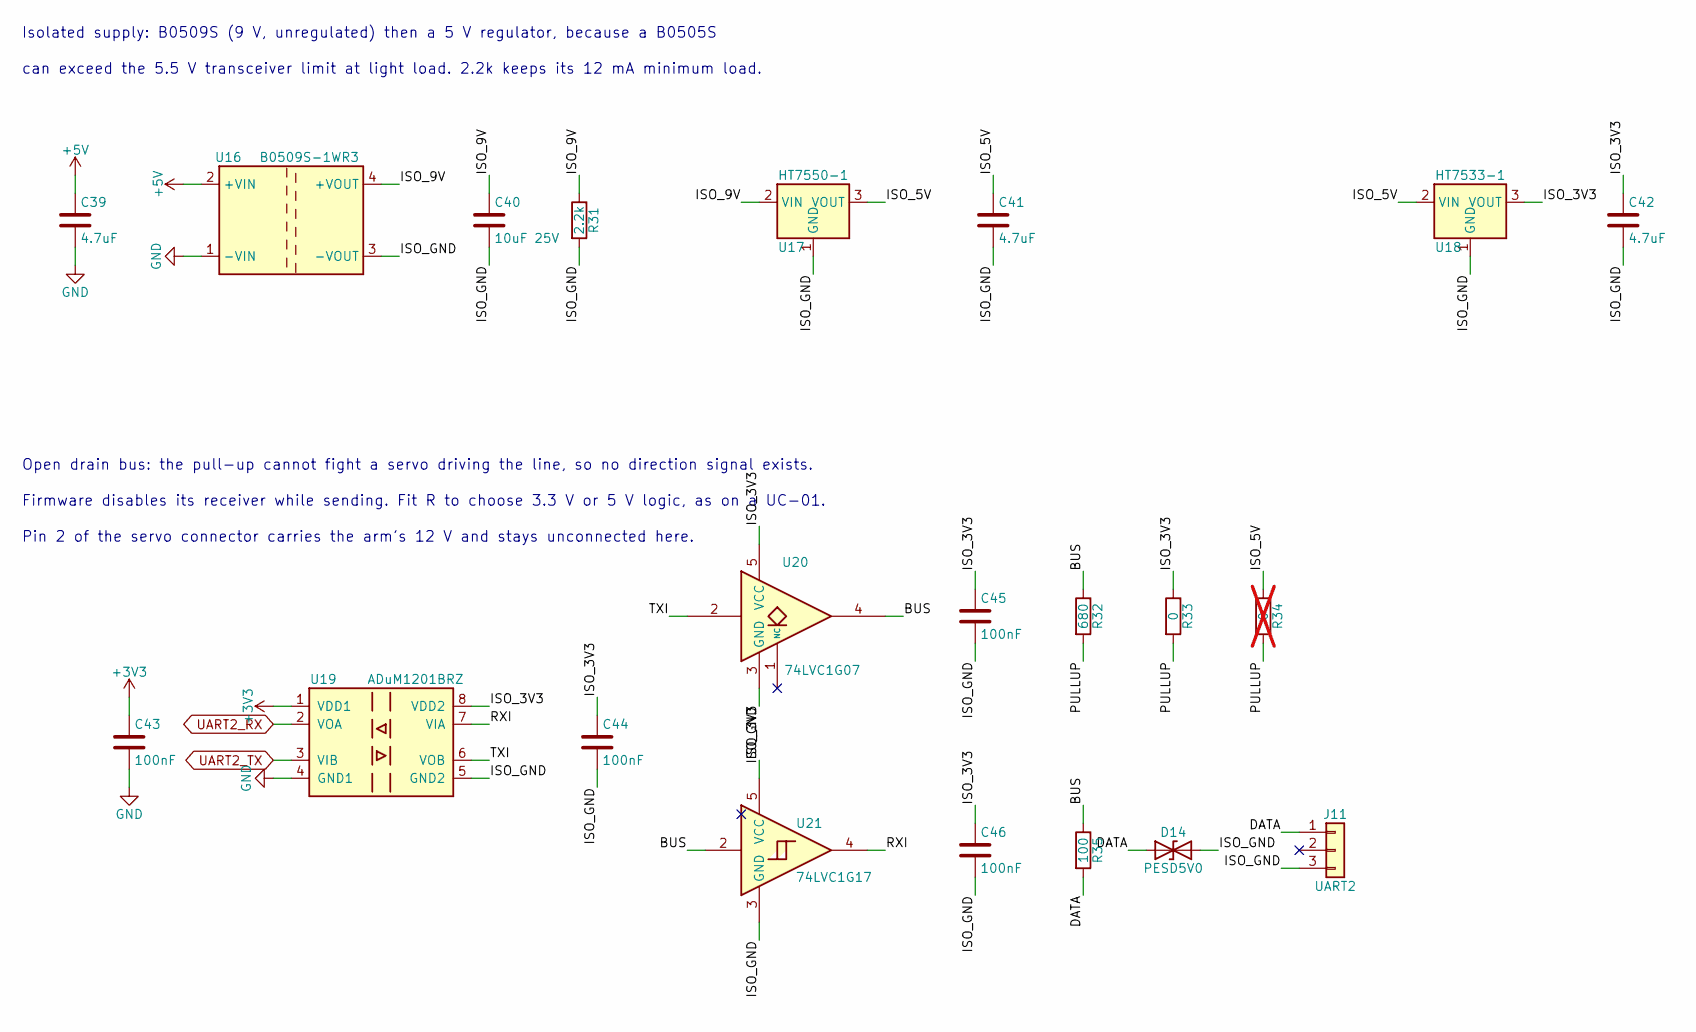
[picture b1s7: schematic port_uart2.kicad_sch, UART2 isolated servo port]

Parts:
C39, C41, C42: 4.7uF; C_0805_2012Metric
C40: 10uF 25V; C_0805_2012Metric
C43, C44, C45, C46: 100nF; C_0603_1608Metric
D14: PESD5V0; D_SOD-323
J11: UART2; JST_PH_B3B-PH-K_1x03_P2.00mm_Vertical
R31: 2.2k; R_0603_1608Metric
R32: 680; R_0603_1608Metric
R33: 0; R_0603_1608Metric
R34: 0; R_0603_1608Metric; not fitted
R35: 100; R_0603_1608Metric
U16: B0509S-1WR3; Converter_DCDC_Murata_CRE1xxxxxxSC_THT; MPN Mornsun B0509S-1WR3
U17: HT7550-1; SOT-89-3; MPN HT7550-1
U18: HT7533-1; SOT-89-3; MPN HT7533-1
U19: ADuM1201BRZ; SOIC-8_3.9x4.9mm_P1.27mm; MPN ADuM1201BRZ
U20: 74LVC1G07; SOT-23-5; MPN SN74LVC1G07DBVR
U21: 74LVC1G17; SOT-23-5; MPN SN74LVC1G17DBVR

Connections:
+3V3: C43.1, U19.1 (VDD1); also elsewhere on the board
+5V: C39.1, U16.2 (+VIN); also elsewhere on the board
/UART2 isolated servo port/BUS: R32.1, R35.1, U20.4, U21.2
/UART2 isolated servo port/DATA: D14.1 (A1), J11.1, R35.2
/UART2 isolated servo port/ISO_3V3: C42.1, C44.1, C45.1, C46.1, R33.1, U18.3 (VOUT), U19.8 (VDD2), U20.5 (VCC), U21.5 (VCC)
/UART2 isolated servo port/ISO_5V: C41.1, R34.1, U17.3 (VOUT), U18.2 (VIN)
/UART2 isolated servo port/ISO_9V: C40.1, R31.1, U16.4 (+VOUT), U17.2 (VIN)
/UART2 isolated servo port/ISO_GND: C40.2, C41.2, C42.2, C44.2, C45.2, C46.2, D14.2 (A2), J11.3, R31.2, U16.3 (-VOUT), U17.1 (GND), U18.1 (GND), U19.5 (GND2), U20.3 (GND), U21.3 (GND)
/UART2 isolated servo port/PULLUP: R32.2, R33.2, R34.2
/UART2 isolated servo port/RXI: U19.7 (VIA), U21.4
/UART2 isolated servo port/TXI: U19.6 (VOB), U20.2
GND: C39.2, C43.2, U16.1 (-VIN), U19.4 (GND1); also elsewhere on the board
UART2_RX: U19.2 (VOA); also elsewhere on the board
UART2_TX: U19.3 (VIB); also elsewhere on the board

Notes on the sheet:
Isolated supply: B0509S (9 V, unregulated) then a 5 V regulator, because a B0505S
can exceed the 5.5 V transceiver limit at light load. 2.2k keeps its 12 mA minimum load.
Open drain bus: the pull-up cannot fight a servo driving the line, so no direction signal exists.
Firmware disables its receiver while sending. Fit R to choose 3.3 V or 5 V logic, as on a UC-01.
Pin 2 of the servo connector carries the arm's 12 V and stays unconnected here.
